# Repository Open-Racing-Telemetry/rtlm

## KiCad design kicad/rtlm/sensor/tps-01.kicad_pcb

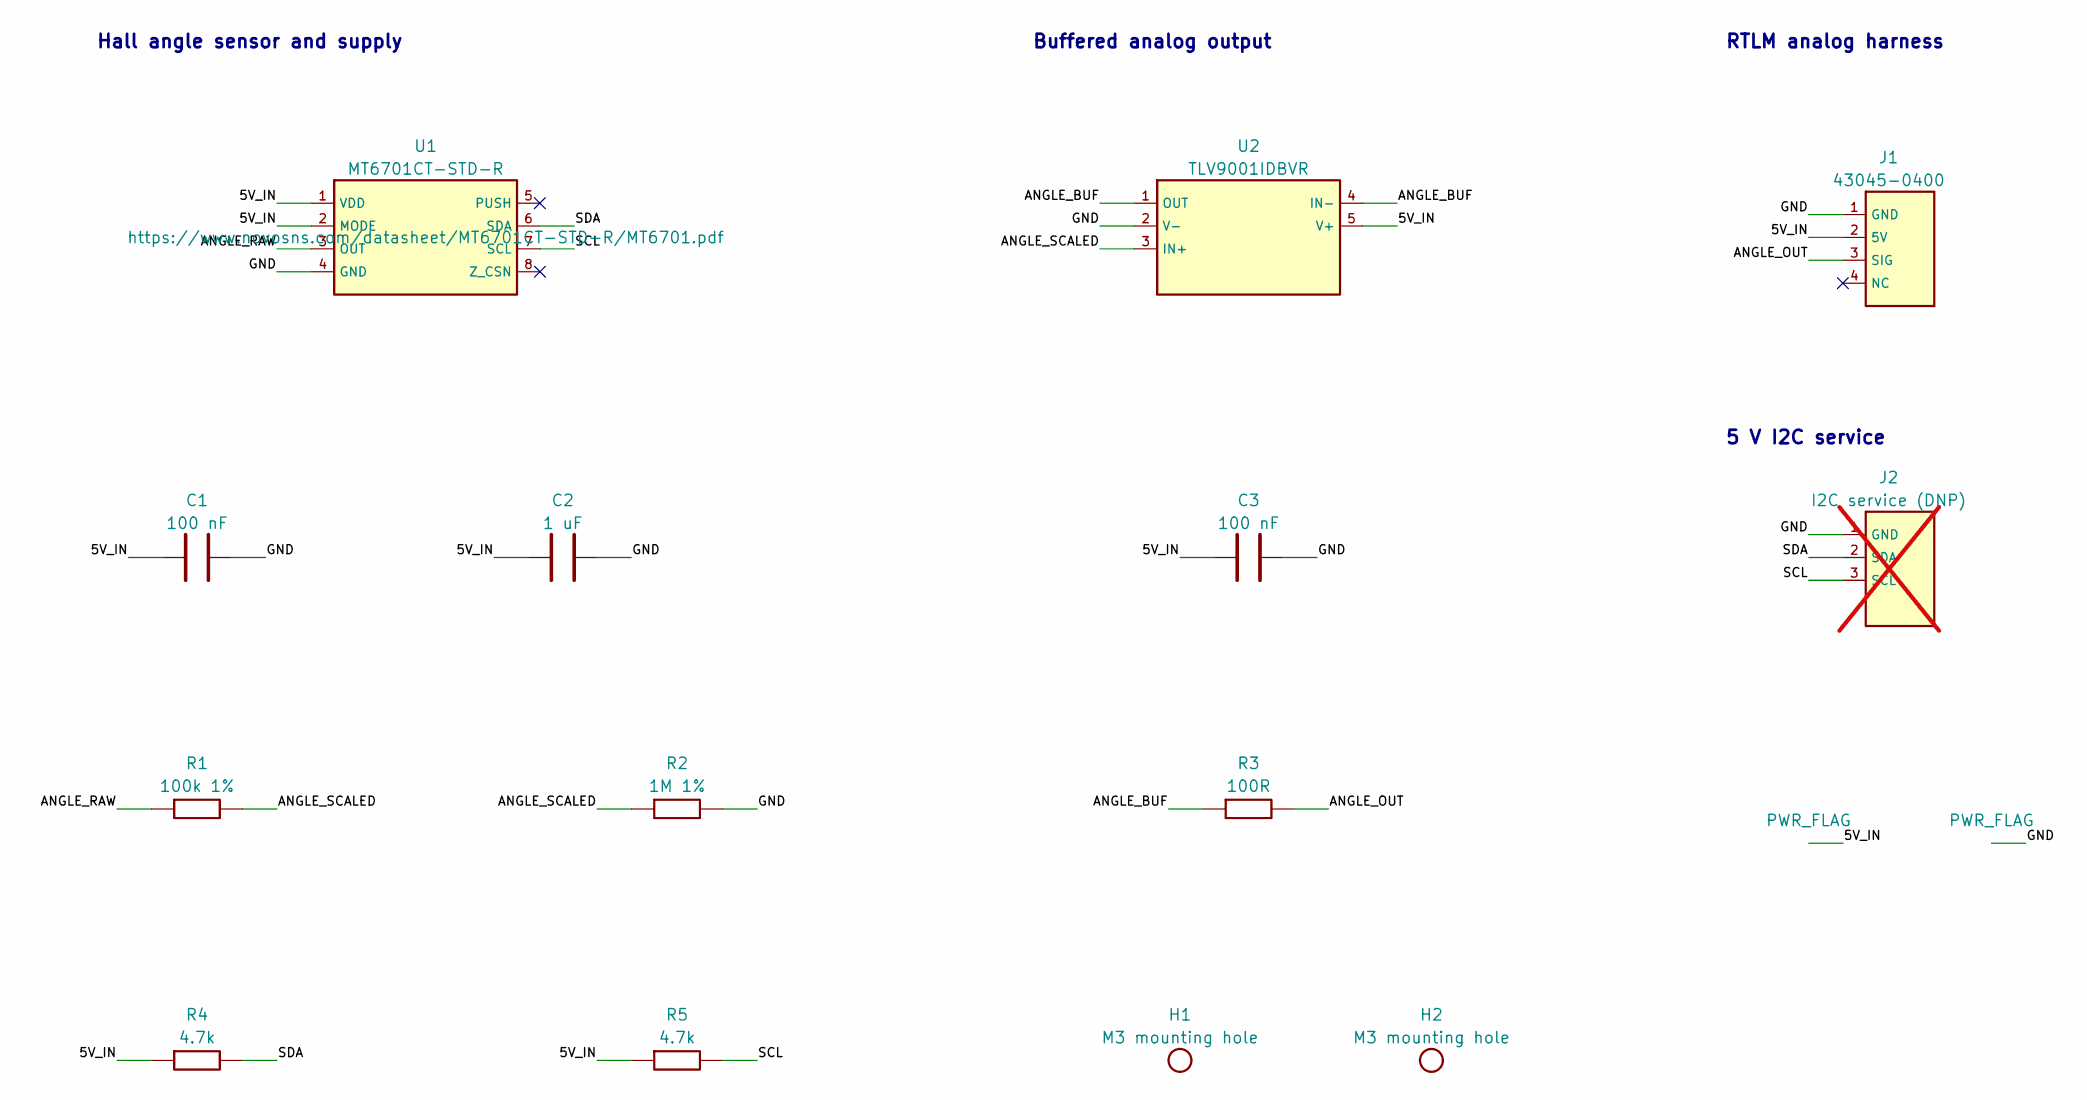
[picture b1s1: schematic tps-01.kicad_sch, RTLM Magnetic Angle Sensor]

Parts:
C1, C3: 100 nF; C_0603_1608Metric; MPN CC0603KRX7R9BB104; LCSC C14663
C2: 1 uF; C_0603_1608Metric; MPN CC0603KRX7R8BB105; LCSC C106858
H1, H2: M3 mounting hole; MountingHole_3.2mm_M3
J1: 43045-0400; Molex_Micro-Fit_3.0_43045-0400_2x02_P3.00mm_Horizontal; MPN 430450400; LCSC C122413
J2: I2C service (DNP); PinHeader_1x03_P2.54mm_Vertical; not fitted
R1: 100k 1%; R_0603_1608Metric; MPN 0603WAF1003T5E; LCSC C25803
R2: 1M 1%; R_0603_1608Metric; MPN 0603WAF1004T5E; LCSC C22935
R3: 100R; R_0603_1608Metric; MPN 0603WAF1000T5E; LCSC C22775
R4, R5: 4.7k; R_0603_1608Metric; MPN 0603WAF4701T5E; LCSC C23162
U1: MT6701CT-STD-R; SOIC-8_3.9x4.9mm_P1.27mm; MPN MT6701CT-STD-R; LCSC C3003196
U2: TLV9001IDBVR; SOT-23-5; MPN TLV9001IDBVR; LCSC C398363

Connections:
/5V_IN: C1.1, C2.1, C3.1, J1.2 (5V), R4.1, R5.1, U1.1 (VDD), U1.2 (MODE), U2.5 (V+)
/ANGLE_BUF: R3.1, U2.1 (OUT), U2.4 (IN-)
/ANGLE_OUT: J1.3 (SIG), R3.2
/ANGLE_RAW: R1.1, U1.3 (OUT)
/ANGLE_SCALED: R1.2, R2.1, U2.3 (IN+)
/GND: C1.2, C2.2, C3.2, J1.1 (GND), J2.1 (GND), R2.2, U1.4 (GND), U2.2 (V-)
/SCL: J2.3 (SCL), R5.2, U1.7 (SCL)
/SDA: J2.2 (SDA), R4.2, U1.6 (SDA)

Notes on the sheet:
RTLM analog harness
Hall angle sensor and supply
Buffered analog output
5 V I2C service

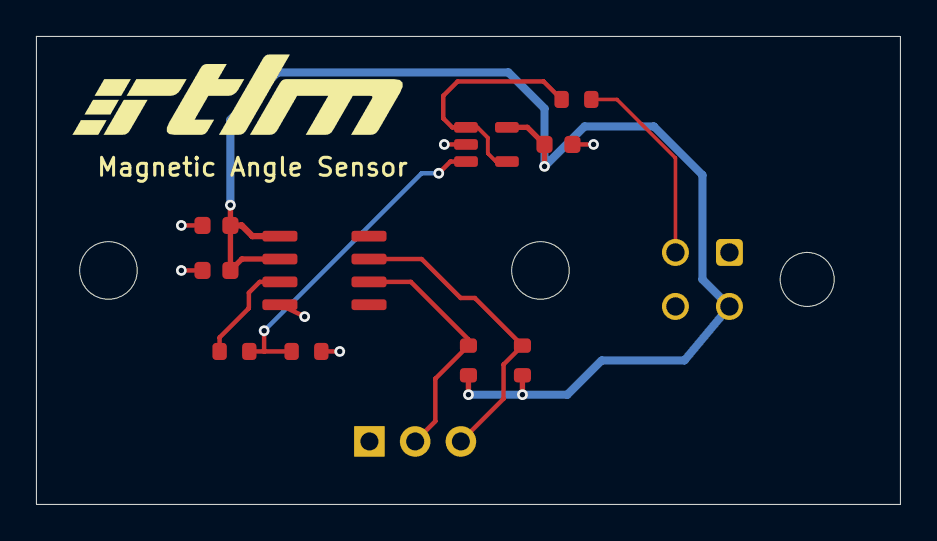
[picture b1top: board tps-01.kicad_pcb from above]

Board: 2 copper layers, 48.0 x 26.0 mm, 14 parts (0 on the bottom side), 8 nets.

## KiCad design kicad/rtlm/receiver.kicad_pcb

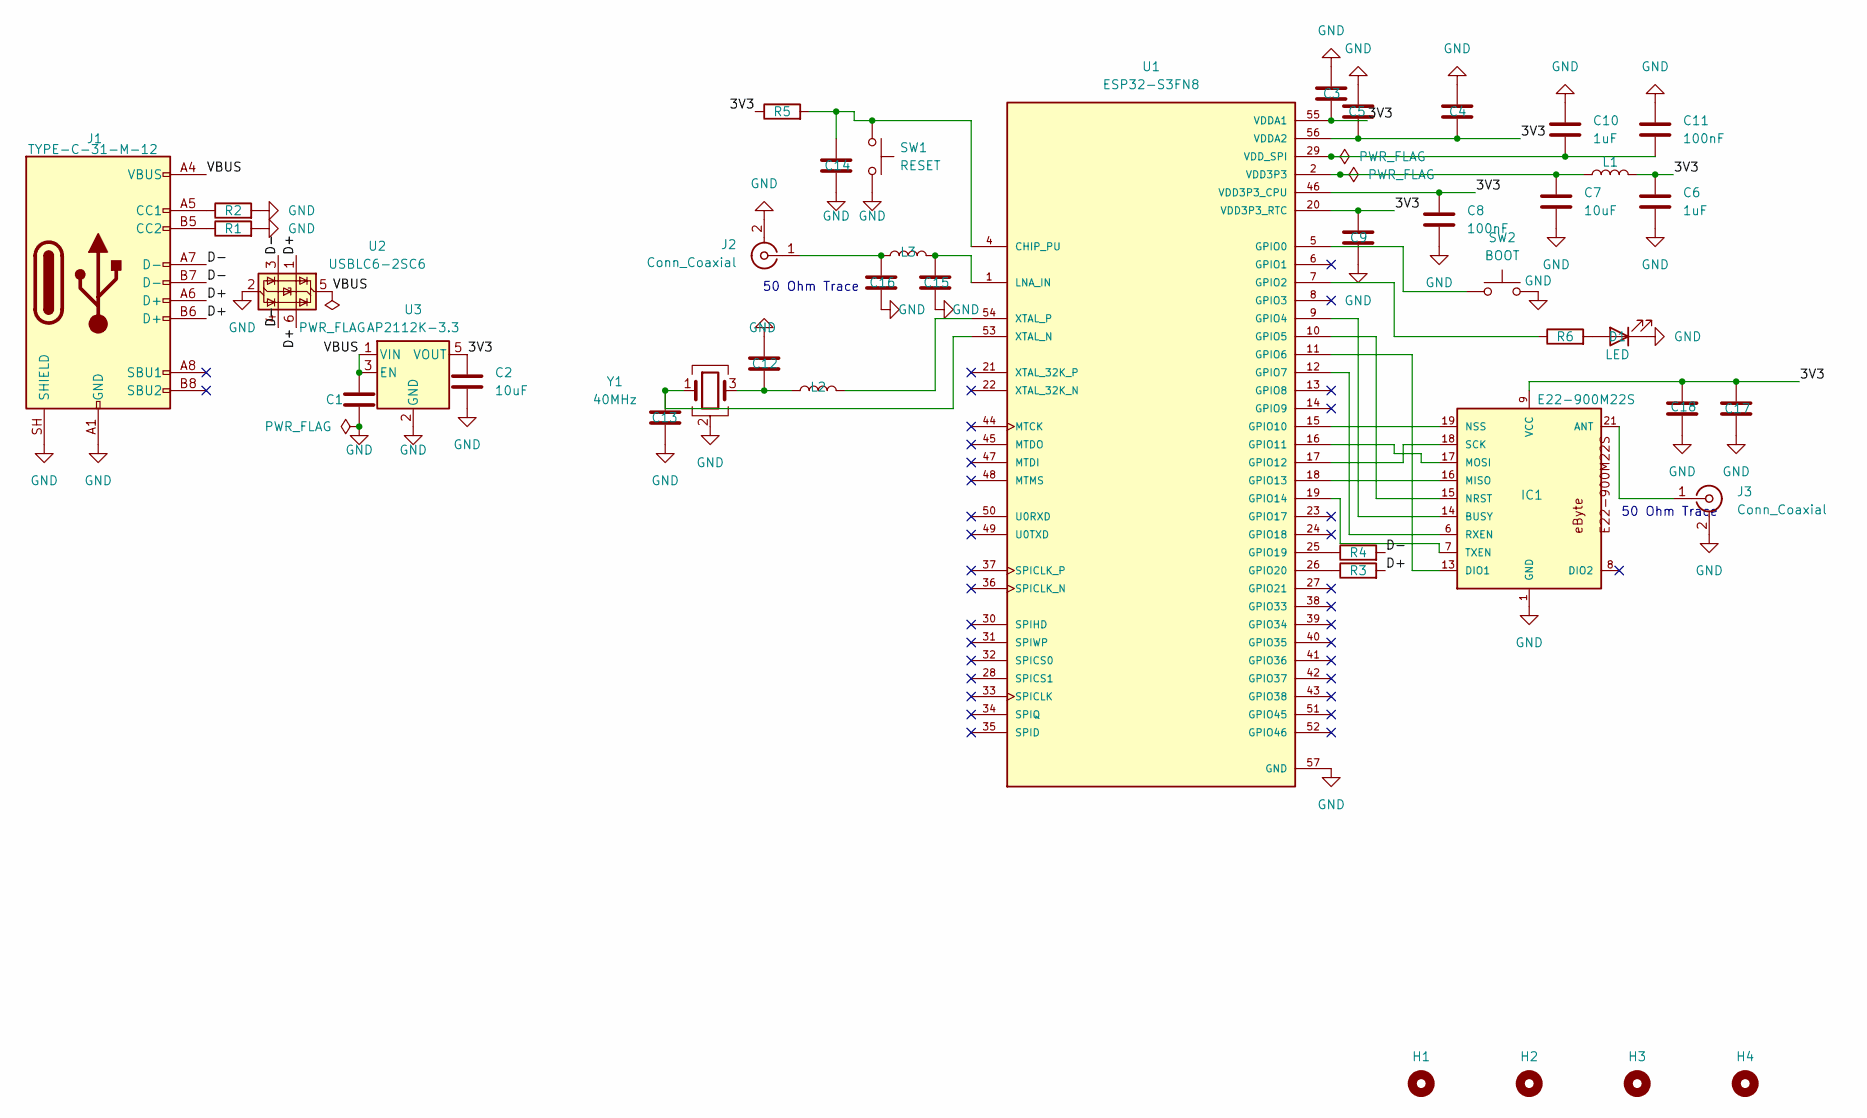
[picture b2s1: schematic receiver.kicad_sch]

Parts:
C1, C2, C4, C7: 10uF; C_0805_2012Metric; MPN CL21A106KAYNNNE; LCSC C15850
C3, C5, C8, C9, C11: 100nF; C_0402_1005Metric; MPN CC0402KRX7R9BB104; LCSC C131394
C6, C10, C14: 1uF; C_0402_1005Metric; MPN CL05A105KA5NQNC; LCSC C52923
C12, C13: 22pF; C_0402_1005Metric; MPN 0402CG220F500NT; LCSC C190090
C15, C16: 1.5pF; C_0402_1005Metric; MPN HH15N1R5B500CT; LCSC C880756
C17: 22uF; C_0805_2012Metric; MPN GRM21BR61E226ME44L; LCSC C86816
C18: 100nF; C_0805_2012Metric; MPN CC0805KRX7R9BB104; LCSC C49678
D1: LED; LED_0603_1608Metric; MPN KT-0603R; LCSC C2286
H1, H2, H3, H4: MountingHole_3.2mm_M3
IC1: E22-900M22S; EBYTE_E22_900M22S; MPN E22-900M22S; LCSC C411293
J1: TYPE-C-31-M-12; USB_C_HRO_TYPE_C_31_M_12_OEM_20201208; MPN TYPE-C-31-M-12; LCSC C165948
J2, J3: Conn_Coaxial; Hirose_UFL_R_SMT_1; MPN U.FL-R-SMT-1(10); LCSC C88373
L1: 2.0nH; L_0603_1608Metric; MPN SDCL1608C2N0STDF; LCSC C370234
L2: 24nH; L_0402_1005Metric; MPN LQW15AN24NH00D; LCSC C913699
L3: 2.4nH; L_0402_1005Metric; MPN LQW15AN2N4B80D; LCSC C3221977
R1, R2: 5.1k; R_0402_1005Metric; MPN 0402WGF5101TCE; LCSC C25905
R3, R4: 22; R_0402_1005Metric; MPN 0402WGF220JTCE; LCSC C25092
R5: 10k; R_0402_1005Metric; MPN 0402WGF1002TCE; LCSC C25744
R6: 1k; R_0402_1005Metric; MPN 0402WGF1001TCE; LCSC C11702
SW1: RESET; SW_Push_1P1T_XKB_TS-1187A; MPN TS-1187A-B-A-B; LCSC C318884
SW2: BOOT; SW_Push_1P1T_XKB_TS-1187A; MPN TS-1187A-B-A-B; LCSC C318884
U1: ESP32-S3FN8; ESP32_S3_QFN56_EP_Windowed; MPN ESP32-S3FN8; LCSC C2913196
U2: USBLC6-2SC6; SOT-23-6; MPN USBLC6-2SC6; LCSC C7519
U3: AP2112K-3.3; SOT-23-5; MPN AP2112K-3.3TRG1; LCSC C51118
Y1: 40MHz; Crystal_SMD_3225-4Pin_3.2x2.5mm; MPN X322540MPB4SI; LCSC C9010

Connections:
/3V3: C2.1, C3.2, C4.2, C5.2, C6.1, C8.1, C9.1, C17.1, C18.1, IC1.9 (VCC), L1.2, R5.1, U1.20 (VDD3P3_RTC), U1.46 (VDD3P3_CPU), U1.55 (VDDA1), U1.56 (VDDA2), U3.5 (VOUT)
/D+: J1.A6 (D+), J1.B6 (D+), R3.2, U2.1 (I/O1), U2.6 (I/O1)
/D-: J1.A7 (D-), J1.B7 (D-), R4.2, U2.3 (I/O2), U2.4 (I/O2)
/VBUS: C1.1, J1.A4 (VBUS), J1.A9 (VBUS), J1.B4 (VBUS), J1.B9 (VBUS), U2.5 (VBUS), U3.1 (VIN), U3.3 (EN)
GND: C1.2, C2.2, C3.1, C4.1, C5.1, C6.2, C7.2, C8.2, C9.2, C10.1, C11.1, C12.2, C13.2, C14.2, C15.2, C16.2, C17.2, C18.2, D1.1 (K), IC1.1 (GND), IC1.2 (GND), IC1.3 (GND), IC1.4 (GND), IC1.5 (GND), IC1.10 (GND), IC1.11 (GND), IC1.12 (GND), IC1.20 (GND), IC1.22 (GND), J1.A1 (GND), J1.A12 (GND), J1.B1 (GND), J1.B12 (GND), J1.SH (SHIELD), J2.2 (Ext), J3.2 (Ext), R1.2, R2.2, SW1.2, SW2.2, U1.57 (GND), U2.2 (GND), U3.2 (GND), Y1.2 (G), Y1.4 (G)
unnamed: C12.1, L2.1, Y1.3
unnamed: D1.2 (A), R6.2
unnamed: IC1.21 (ANT), J3.1 (In)
unnamed: IC1.14 (BUSY), U1.9 (GPIO4)
unnamed: IC1.13 (DIO1), U1.11 (GPIO6)
unnamed: IC1.16 (MISO), U1.18 (GPIO13)
unnamed: IC1.17 (MOSI), U1.16 (GPIO11)
unnamed: IC1.15 (NRST), U1.10 (GPIO5)
unnamed: IC1.19 (NSS), U1.15 (GPIO10)
unnamed: IC1.6 (RXEN), U1.12 (GPIO7)
unnamed: IC1.18 (SCK), U1.17 (GPIO12)
unnamed: IC1.7 (TXEN), U1.19 (GPIO14)
unnamed: J1.A5 (CC1), R2.1
unnamed: J1.B5 (CC2), R1.1
unnamed: C16.1, J2.1 (In), L3.1
unnamed: C14.1, R5.2, SW1.1, U1.4 (CHIP_PU)
unnamed: SW2.1, U1.5 (GPIO0)
unnamed: R6.1, U1.7 (GPIO2)
unnamed: R4.1, U1.25 (GPIO19)
unnamed: R3.1, U1.26 (GPIO20)
unnamed: C15.1, L3.2, U1.1 (LNA_IN)
unnamed: C10.2, C11.2, U1.29 (VDD_SPI)
unnamed: C13.1, U1.53 (XTAL_N), Y1.1
unnamed: L2.2, U1.54 (XTAL_P)
VDD3P3: C7.1, L1.1, U1.2 (VDD3P3), U1.3 (VDD3P3)

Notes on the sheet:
50 Ohm Trace

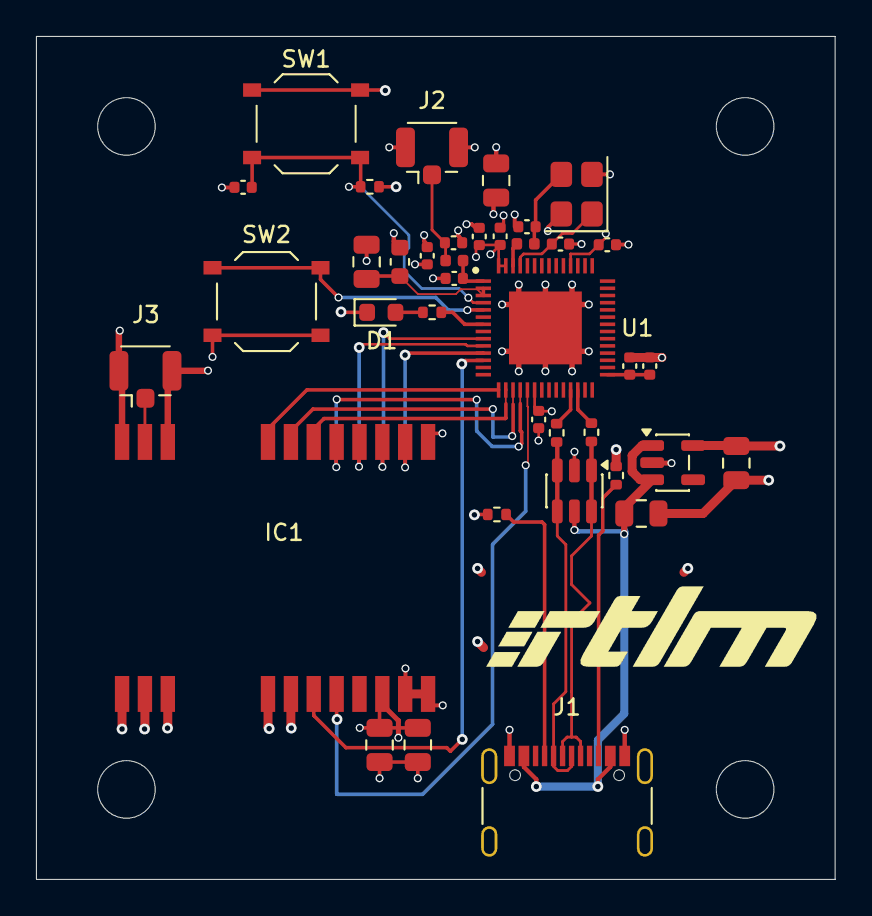
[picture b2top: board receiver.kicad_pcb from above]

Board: 4 copper layers, 44.4 x 46.8 mm, 42 parts (0 on the bottom side), 30 nets.
